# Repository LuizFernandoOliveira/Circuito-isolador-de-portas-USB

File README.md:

# Circuito isolador de portas USB

## Descrição
Este circuito foi desenvolvido com o propósito de realizar uma isolação digital de 3,75 kV RMS para USB 2.0 de alta e baixa velocidade.

---

## Descrições técnicas

- Sinalização USB 2.0 com detecção automática de conexões de baixa, plena e alta velocidade;
- Taxas de dados de 1,5 Mbps, 12 Mbps e 480 Mbps;
- Isolador USB bidirecional para portas upstream e downstream;
- Recondicionamento e retiming de dados em alta velocidade para remoção de jitter de entrada;
- Modo de espera de ultrabaixo consumo em suspensão (L2) ou desconexão USB 2.0;
- Corrente típica de espera de baixa potência no lado upstream: 1,7 mA;
- Corrente típica de espera de baixa potência no lado downstream: 20 μA;
- Proteção ESD de ±6000 V conforme a norma IEC 61000-4-2, através da barreira de isolação;
- Atende aos requisitos de emissão da norma CISPR32/EN55032 Classe B;
- Alta imunidade a transientes de modo comum: 50 kV/μs (típico).

---

## Estrutura do repositório
Os arquivos de hardware foram desenvolvidos utilizando o KiCad 9.0.
- **`.kicad_pcb`**: Layout da placa de circuito impresso (Board).
- **`.kicad_sch`**: Esquemático eletrônico do sistema (Schematic).
- **`.kicad_pro`**: Gerenciador de projeto do KiCad (Project).

---

## Autor
**Dr. Luiz Fernando Pinto de Oliveira**

*Engenheiro Eletrônico especializado em Sistemas Embarcados e Ultra-Low Power.*
- **Website:** [FAPLO](https://faplo.webnode.page/)
- **LinkedIn:** [lfpo](https://www.linkedin.com/in/lfpo/)

---

Shield: [![CC BY-NC-ND 4.0][cc-by-nc-nd-shield]][cc-by-nc-nd]

This work is licensed under a
[Creative Commons Attribution-NonCommercial-NoDerivs 4.0 International License][cc-by-nc-nd].

[![CC BY-NC-ND 4.0][cc-by-nc-nd-image]][cc-by-nc-nd]

[cc-by-nc-nd]: http://creativecommons.org/licenses/by-nc-nd/4.0/
[cc-by-nc-nd-image]: https://licensebuttons.net/l/by-nc-nd/4.0/88x31.png
[cc-by-nc-nd-shield]: https://img.shields.io/badge/License-CC%20BY--NC--ND%204.0-lightgrey.svg

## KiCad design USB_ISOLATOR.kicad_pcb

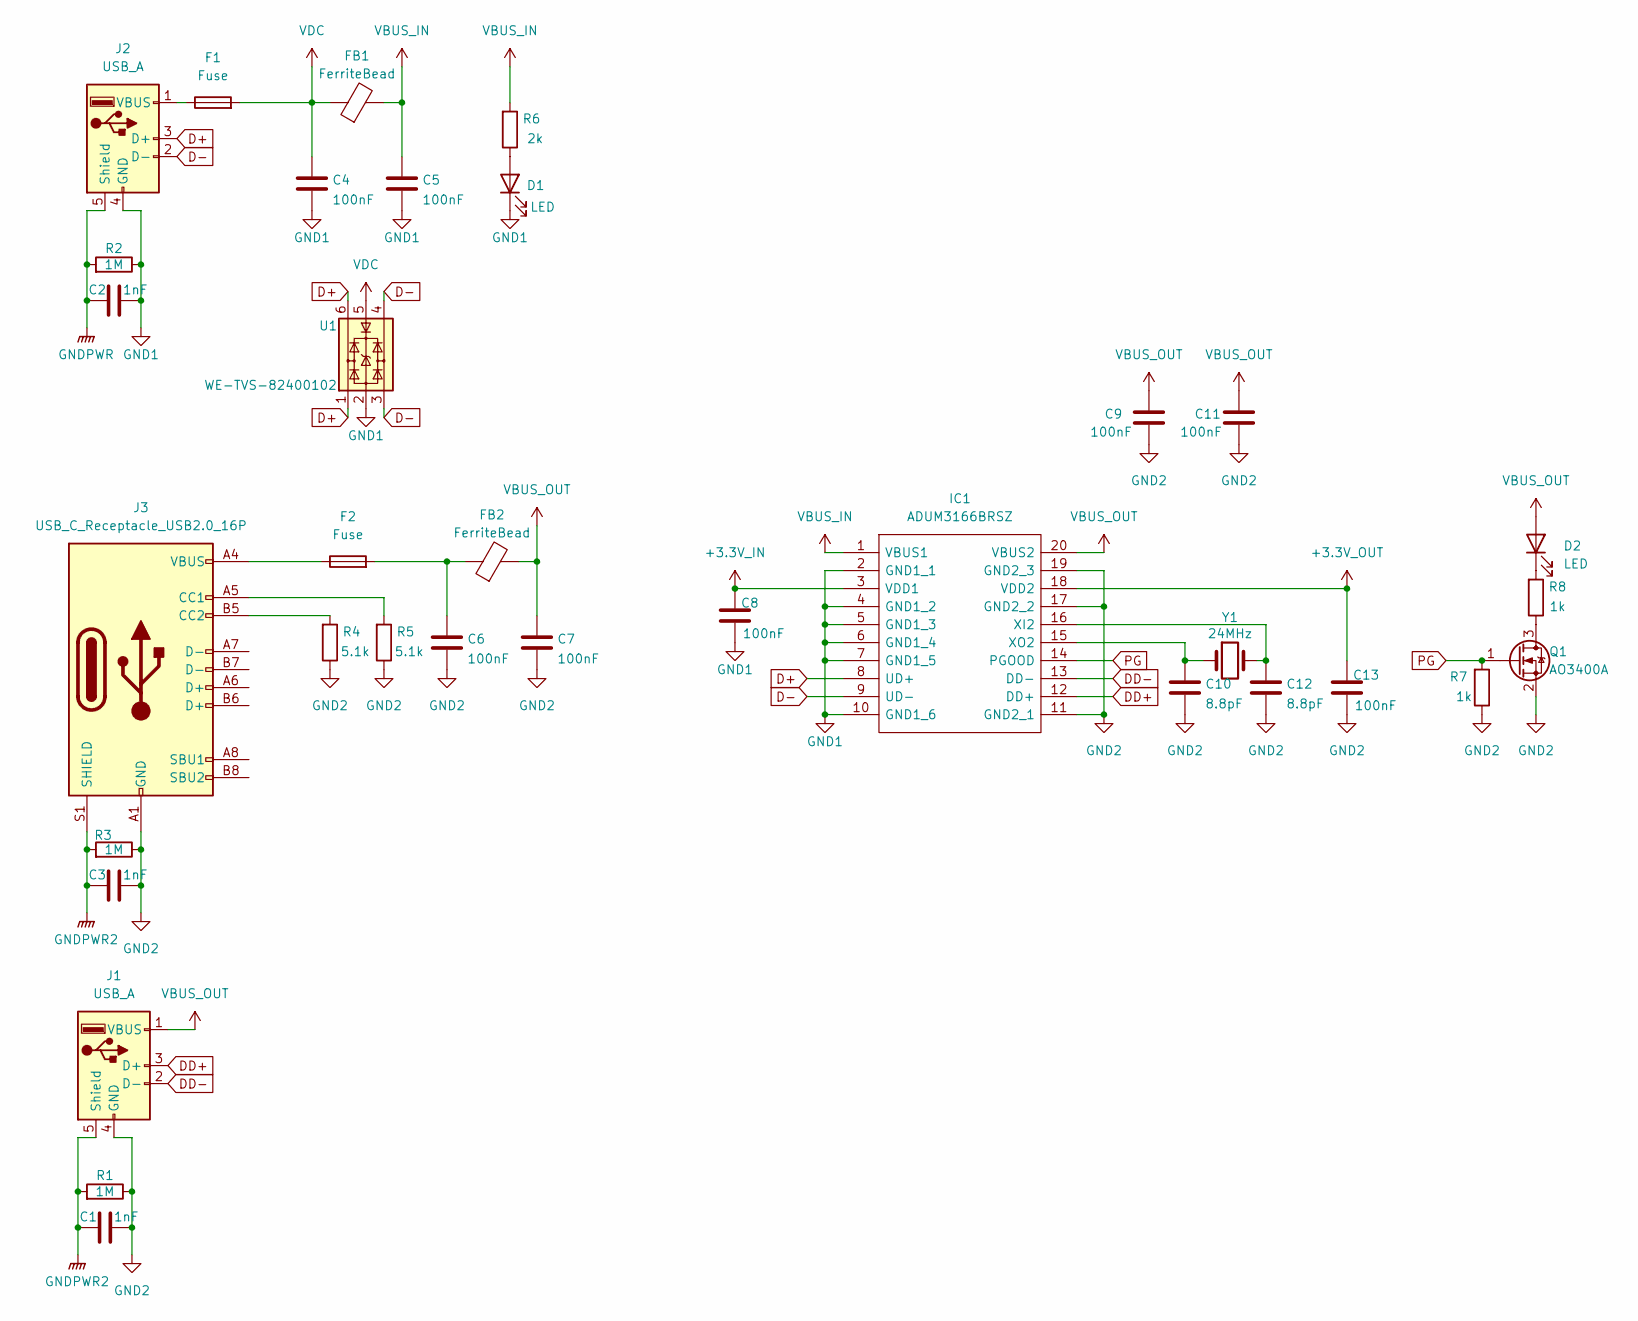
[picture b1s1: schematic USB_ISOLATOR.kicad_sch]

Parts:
C1, C2, C3: 1nF; C_0805_2012Metric
C4, C5, C6, C7, C8, C9, C11, C13: 100nF; C_0805_2012Metric
C10, C12: 8.8pF; C_0805_2012Metric
D1, D2: LED; LED_0805_2012Metric
F1, F2: Fuse; Fuse_0805_2012Metric
FB1, FB2: FerriteBead; L_0805_2012Metric
IC1: ADUM3166BRSZ; SOP65P780X200-20N; Manufacturer_Part_Number ADUM3166BRSZ; Mouser Part Number 584-ADUM3166BRSZ
J1: USB_A; USB_A_TE_292303-7_Horizontal
J2: USB_A; USB_A_CNCTech_1001-011-01101_Horizontal
J3: USB_C_Receptacle_USB2.0_16P; USB_C_Receptacle_HRO_TYPE-C-31-M-12
Q1: AO3400A; SOT-23
R1, R2, R3: 1M; R_0805_2012Metric
R4, R5: 5.1k; R_0805_2012Metric
R6: 2k; R_0805_2012Metric
R7, R8: 1k; R_0805_2012Metric
U1: WE-TVS-82400102; SOT-23-6
Y1: 24MHz; R_0805_2012Metric

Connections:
+3.3V_IN: C8.1, IC1.3 (VDD1)
+3.3V_OUT: C13.1, IC1.18 (VDD2)
D+: IC1.8 (UD+), J2.3 (D+), U1.1, U1.6
D-: IC1.9 (UD-), J2.2 (D-), U1.3, U1.4
DD+: IC1.12 (DD+), J1.3 (D+)
DD-: IC1.13 (DD-), J1.2 (D-)
GND1: C2.2, C4.2, C5.2, C8.2, D1.1 (K), IC1.2 (GND1_1), IC1.4 (GND1_2), IC1.5 (GND1_3), IC1.6 (GND1_4), IC1.7 (GND1_5), IC1.10 (GND1_6), J2.4 (GND), R2.1, U1.2
GND2: C1.2, C3.2, C6.2, C7.2, C9.2, C10.2, C11.2, C12.2, C13.2, IC1.11 (GND2_1), IC1.17 (GND2_2), IC1.19 (GND2_3), J1.4 (GND), J3.A1 (GND), J3.A12 (GND), J3.B1 (GND), J3.B12 (GND), Q1.2 (S), R1.1, R3.1, R4.1, R5.1, R7.1
GNDPWR: C2.1, J2.5 (Shield), R2.2
GNDPWR2: C1.1, C3.1, J1.5 (Shield), J3.S1 (SHIELD), R1.2, R3.2
unnamed: C6.1, F2.2, FB2.1
unnamed: D1.2 (A), R6.1
unnamed: D2.1 (K), R8.2
unnamed: F2.1, J3.A4 (VBUS), J3.A9 (VBUS), J3.B4 (VBUS), J3.B9 (VBUS)
unnamed: C12.1, IC1.16 (XI2), Y1.2
unnamed: C10.1, IC1.15 (XO2), Y1.1
unnamed: F1.1, J2.1 (VBUS)
unnamed: J3.A5 (CC1), R5.2
unnamed: J3.B5 (CC2), R4.2
unnamed: Q1.3 (D), R8.1
PG: IC1.14 (PGOOD), Q1.1 (G), R7.2
VBUS_IN: C5.1, FB1.2, IC1.1 (VBUS1), R6.2
VBUS_OUT: C7.1, C9.1, C11.1, D2.2 (A), FB2.2, IC1.20 (VBUS2), J1.1 (VBUS)
VDC: C4.1, F1.2, FB1.1, U1.5

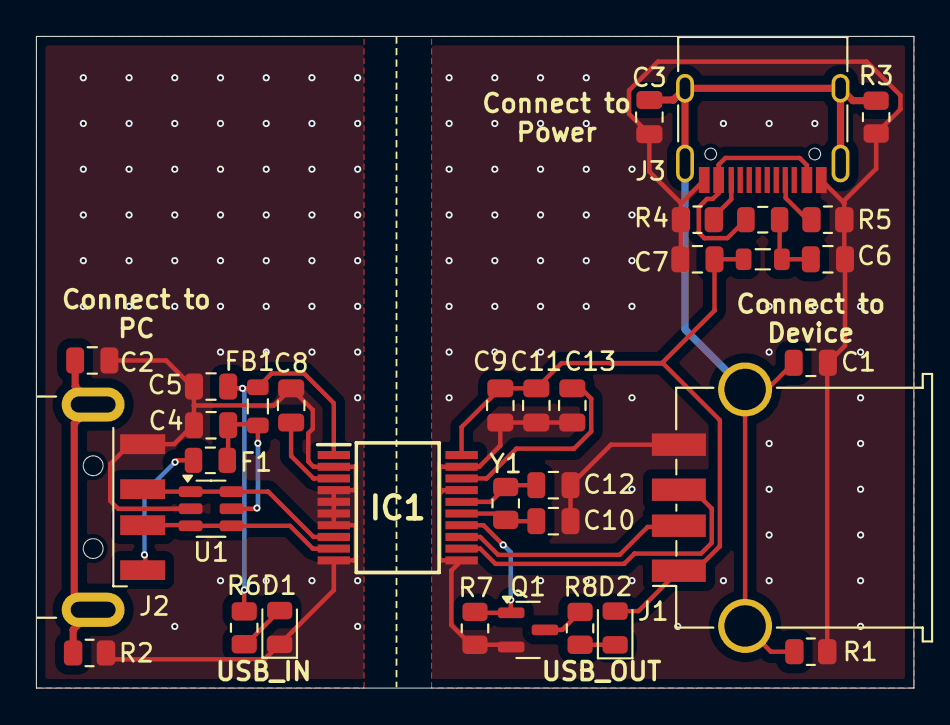
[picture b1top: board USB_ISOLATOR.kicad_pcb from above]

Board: 2 copper layers, 48.8 x 36.2 mm, 34 parts (0 on the bottom side), 24 nets.

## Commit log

2026-04-17 Inicialização do repositório
2026-04-17 Update README with project status and technical details
    Added project status and detailed technical descriptions.
2026-04-17 Add LICENSE file with Creative Commons license
    Added Creative Commons Attribution-NonCommercial-NoDerivatives 4.0 International Public License to the project.
